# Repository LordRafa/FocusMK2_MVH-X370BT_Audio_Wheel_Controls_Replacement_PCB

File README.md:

Replacement PCB for the FocusMK2 Wheel Audio Controls to control the MVH-X370BT

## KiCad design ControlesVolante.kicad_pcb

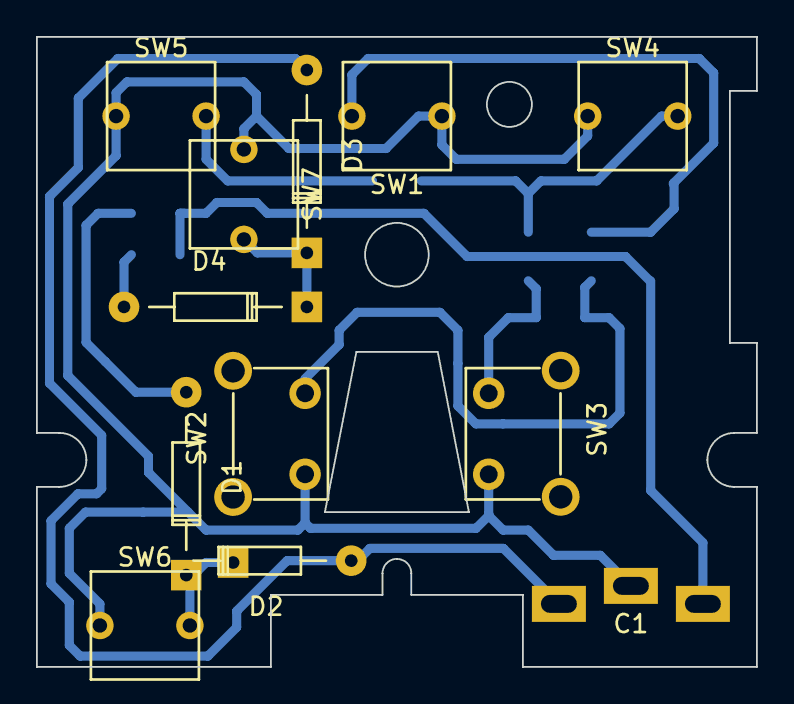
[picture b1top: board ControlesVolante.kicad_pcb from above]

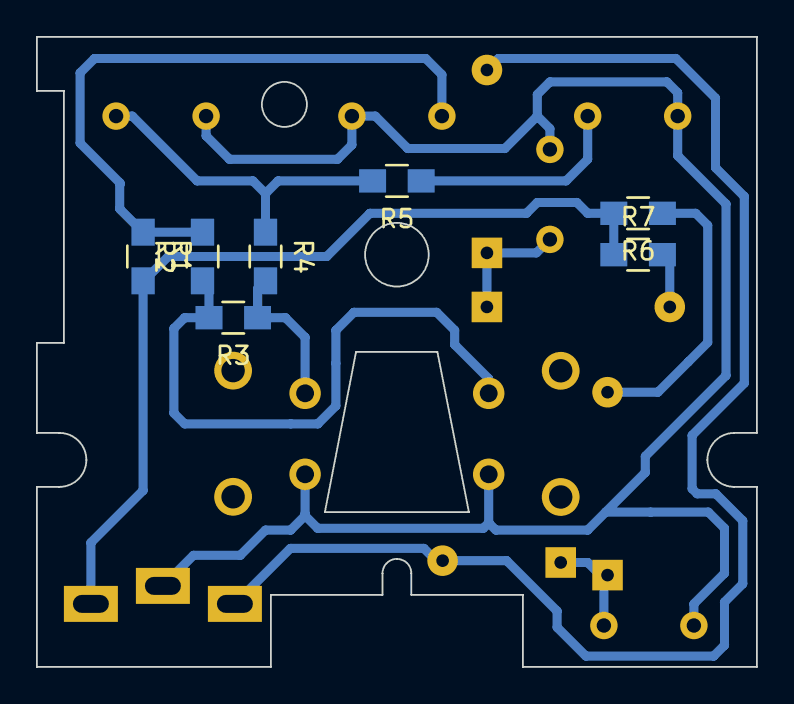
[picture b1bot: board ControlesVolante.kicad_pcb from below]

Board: 2 copper layers, 40.0 x 35.0 mm, 19 parts (7 on the bottom side), 12 nets.

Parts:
C1: FordConn
D1, D2, D3, D4: 1N5818; Diode_DO-35_SOD27_Horizontal_RM10
R1, R2, R3, R4, R5, R6, R7: R; R_0805_HandSoldering
SW1: Mode; FordPushSW
SW2: TrackUp; FordVerticalSW
SW3: TrackDown; FordVerticalSW
SW4: VolUp; FordPushSW
SW5: VolDown; FordPushSW
SW6: PhoneAnswer; FordPushSW
SW7: PhoneHang; FordPushSW

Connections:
unnamed: C1.1, R1.2, R6.2, R7.1
unnamed: C1.2, SW1.2, SW2.2, SW3.1, SW4.2, SW5.2, SW6.2, SW7.2
unnamed: C1.3, D2.2, D3.2
unnamed: D1.1, D2.1, SW6.1
unnamed: D1.2, R6.1
unnamed: D3.1, D4.1, SW7.1
unnamed: D4.2, R7.2
unnamed: R1.1, R2.2, SW1.1
unnamed: R2.1, R3.2, SW2.1
unnamed: R3.1, R4.2, SW3.2
unnamed: R4.1, R5.2, SW4.1
unnamed: R5.1, SW5.1

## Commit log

2021-05-04 Wheel Audio Controls
